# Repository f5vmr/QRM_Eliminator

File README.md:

A mistake in the downloaded zip file!!
The PCB is not designed with Diptrace but with KiCad and the version it was made with can be down loaded free from here - https://www.filehorse.com/download-kicad/55035/download/#google_vignette

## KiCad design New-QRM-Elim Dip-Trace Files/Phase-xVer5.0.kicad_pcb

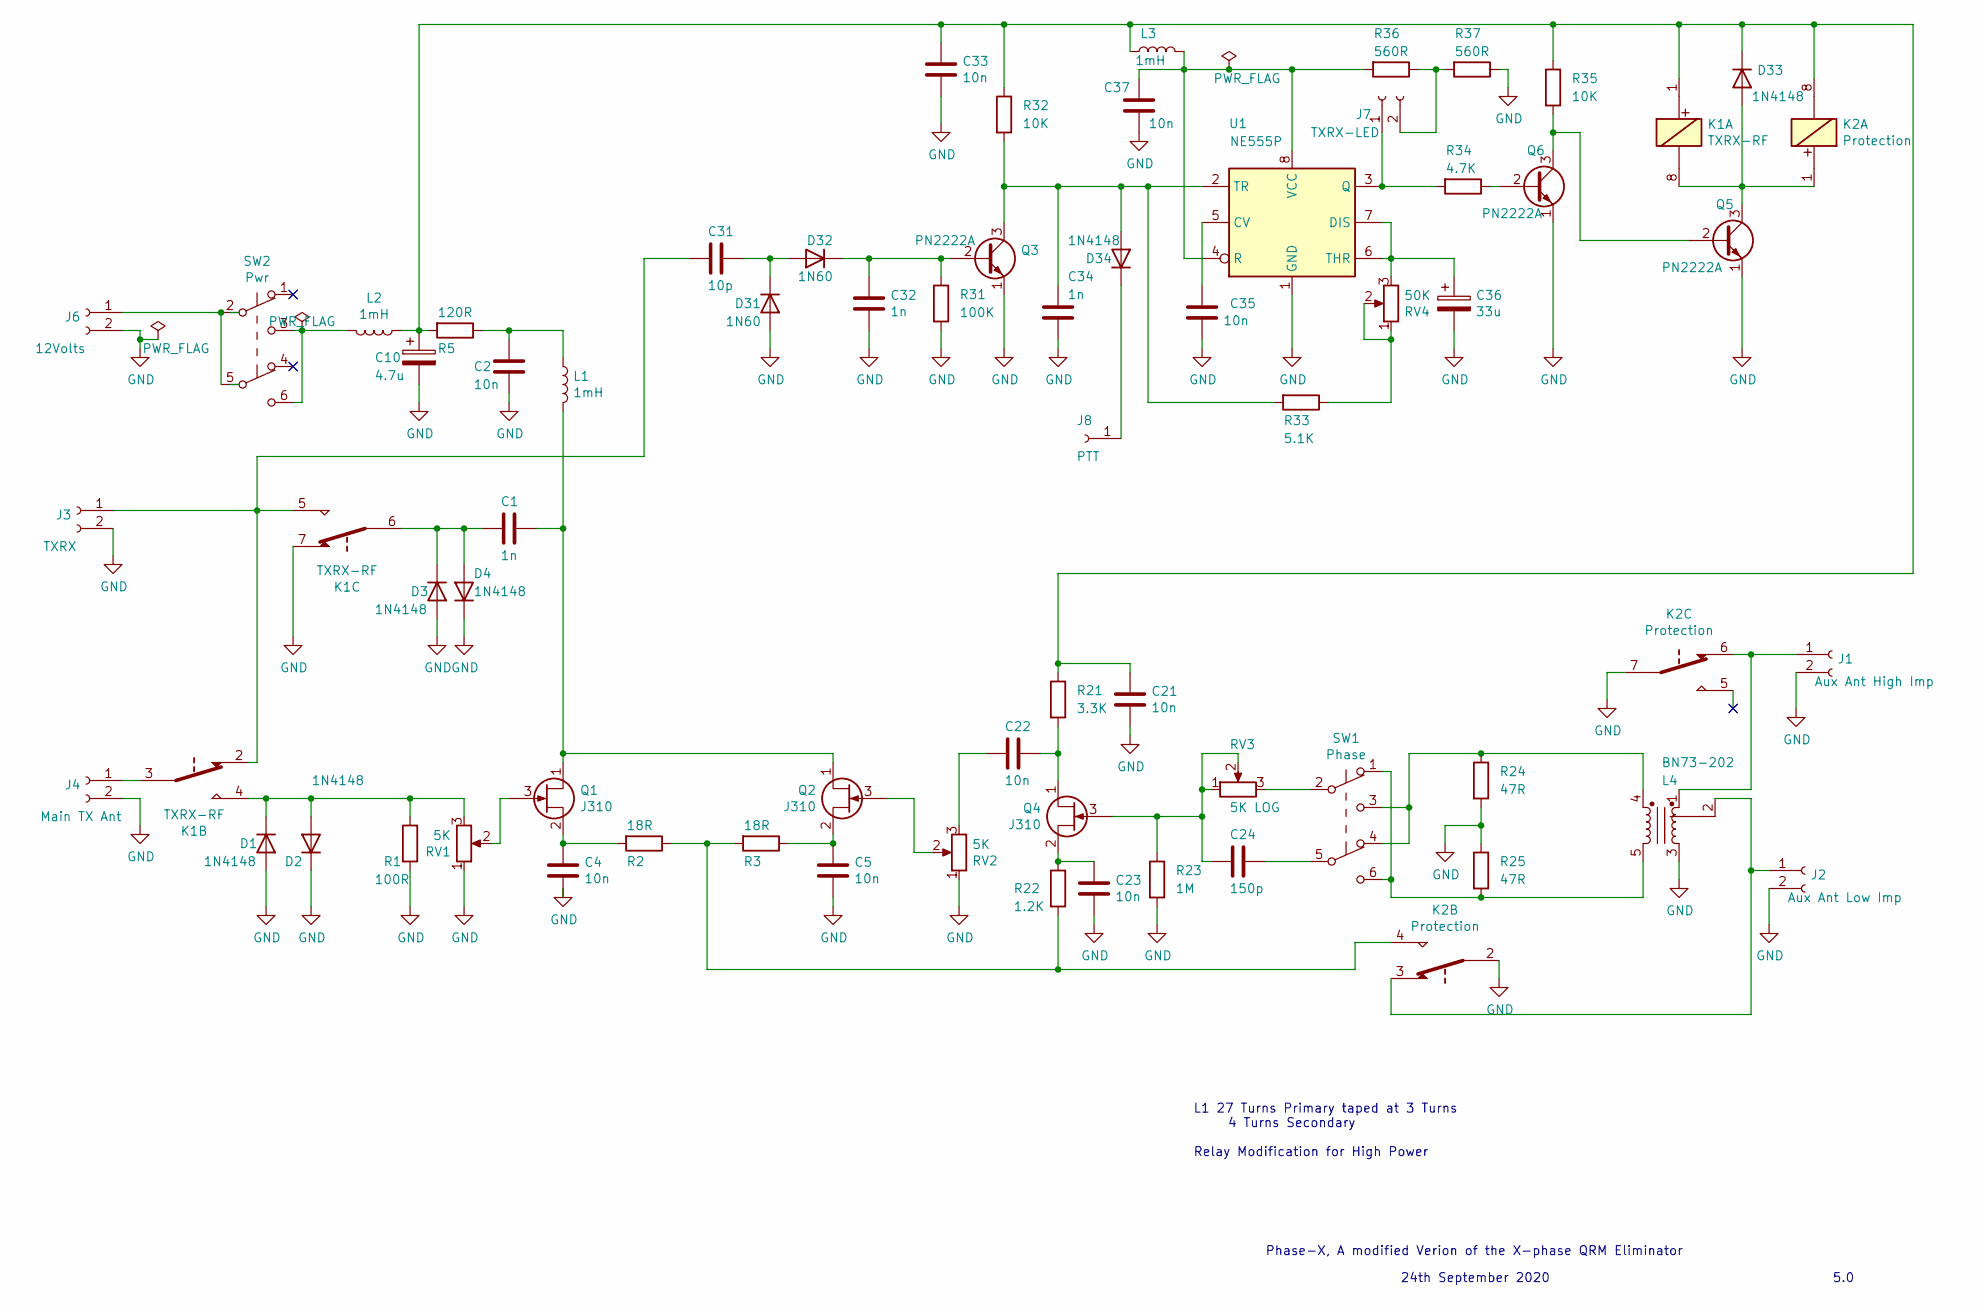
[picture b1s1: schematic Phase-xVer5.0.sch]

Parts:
C1, C32, C34: 1n; CeramicDisc_P5.0mm
C2, C4, C5, C21, C22, C23, C33, C35, C37: 10n; CeramicDisc_P5.0mm
C10: 4.7u; Small_Tant_Elect
C24: 150p; CeramicDisc_P7.5_3pin
C31: 10p; CeramicDisc_P5.0mm
C36: 33u; Small_Tant_Elect
D1, D2, D3, D4, D33, D34: 1N4148; Signal_Diode
D31, D32: 1N60; Signal_Diode
J1: Aux Ant High Imp; Connector
J2: Aux Ant Low Imp; Connector
J3: TXRX; Connector
J4: Main TX Ant; Connector
J6: 12Volts; 2Pin_Molex
J7: TXRX-LED; 2Pin_Molex
J8: PTT; SingleConnector
K1: TXRX-RF; Relay_DPDT_Omron_G2RL
K2: Protection; Relay_DPDT_Omron
L1, L2, L3: 1mH; Inductor
L4: BN73-202
Q1, Q2, Q4: J310; TO-92_Wide
Q3, Q5, Q6: PN2222A; TO-92_Wide
R1: 100R; R_L6.3mm__P10.16mm_Pad2.2mm
R2, R3: 18R; R_L6.3mm__P10.16mm_Pad2.2mm
R5: 120R; R_L6.3mm__P10.16mm_Pad2.2mm
R21: 3.3K; R_L6.3mm__P10.16mm_Pad2.2mm
R22: 1.2K; R_L6.3mm__P10.16mm_Pad2.2mm
R23: 1M; R_L6.3mm__P10.16mm_Pad2.2mm
R24, R25: 47R; R_L6.3mm__P10.16mm_Pad2.2mm
R31: 100K; R_L6.3mm__P10.16mm_Pad2.2mm
R32, R35: 10K; R_L6.3mm__P10.16mm_Pad2.2mm
R33: 5.1K; R_L6.3mm__P10.16mm_Pad2.2mm
R34: 4.7K; R_L6.3mm__P10.16mm_Pad2.2mm
R36, R37: 560R; R_L6.3mm__P10.16mm_Pad2.2mm
RV1, RV2: 5K; Potentiometer_T-16H_Single_Horizontal
RV3: 5K LOG; Potentiometer_T-16H_Single_Horizontal
RV4: 50K; Preset
SW1: Phase; SW_Push_DPDT-P0.1mil
SW2: Pwr; SW_Push_DPDT-P0.1mil
U1: NE555P; DIP8

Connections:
GND: C2.2, C4.2, C5.2, C10.2, C21.2, C23.2, C32.2, C33.2, C34.2, C35.2, C36.2, C37.2, D1.2 (A), D2.1 (K), D3.2 (A), D4.1 (K), D31.2 (A), J1.2, J2.2, J3.2, J4.2, J6.2, K1.7, K2.2, K2.7, L4.3, Q3.1 (E), Q5.1 (E), Q6.1 (E), R1.2, R23.2, R24.2, R25.1, R31.2, R37.1, RV1.1, RV2.1, U1.1 (GND)
unnamed: C1.1, L1.2, Q1.1 (D), Q2.1 (D)
unnamed: C1.2, D3.1 (K), D4.2 (A), K1.6
unnamed: C2.1, L1.1, R5.1
unnamed: C4.1, Q1.2 (S), R2.2
unnamed: C5.1, Q2.2 (S), R3.1
unnamed: C10.1, C21.1, C33.1, D33.1 (K), K1.1, K2.8, L2.1, L3.1, R5.2, R21.1, R32.1, R35.1
unnamed: C22.1, Q4.1 (D), R21.2
unnamed: C22.2, RV2.3
unnamed: C23.1, Q4.2 (S), R22.1
unnamed: C24.1, SW1.5 (B)
unnamed: C24.2, Q4.3 (G), R23.1, RV3.1, RV3.2
unnamed: C31.1, D31.1 (K), D32.2 (A)
unnamed: C31.2, J3.1, K1.2, K1.5
unnamed: C32.1, D32.1 (K), Q3.2 (B), R31.1
unnamed: C34.1, D34.2 (A), Q3.3 (C), R32.2, R33.2, U1.2 (TR)
unnamed: C35.1, U1.5 (CV)
unnamed: C36.1, RV4.3, U1.6 (THR), U1.7 (DIS)
unnamed: C37.1, L3.2, R36.2, U1.4 (R), U1.8 (VCC)
unnamed: D1.1 (K), D2.2 (A), K1.4, R1.1, RV1.3
unnamed: D33.2 (A), K1.8, K2.1, Q5.3 (C)
unnamed: D34.1 (K), J8.1
unnamed: J1.1, K2.6, L4.1
unnamed: J2.1, K2.3, L4.2
unnamed: J4.1, K1.3
unnamed: J6.1, SW2.2 (B), SW2.5 (B)
unnamed: J7.1, R34.2, U1.3 (Q)
unnamed: J7.2, R36.1, R37.2
unnamed: K2.4, R2.1, R3.2, R22.2
unnamed: L2.2, SW2.3 (C), SW2.6 (C)
unnamed: L4.4, R24.1, SW1.3 (C), SW1.4 (A)
unnamed: L4.5, R25.2, SW1.1 (A), SW1.6 (C)
unnamed: Q1.3 (G), RV1.2
unnamed: Q2.3 (G), RV2.2
unnamed: Q5.2 (B), Q6.3 (C), R35.2
unnamed: Q6.2 (B), R34.1
unnamed: R33.1, RV4.1, RV4.2
unnamed: RV3.3, SW1.2 (B)

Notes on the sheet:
L1 27 Turns Primary taped at 3 Turns 4 Turns Secondary Relay Modification for High Power
Phase-X, A modified Verion of the X-phase QRM Eliminator
5.0
24th September 2020

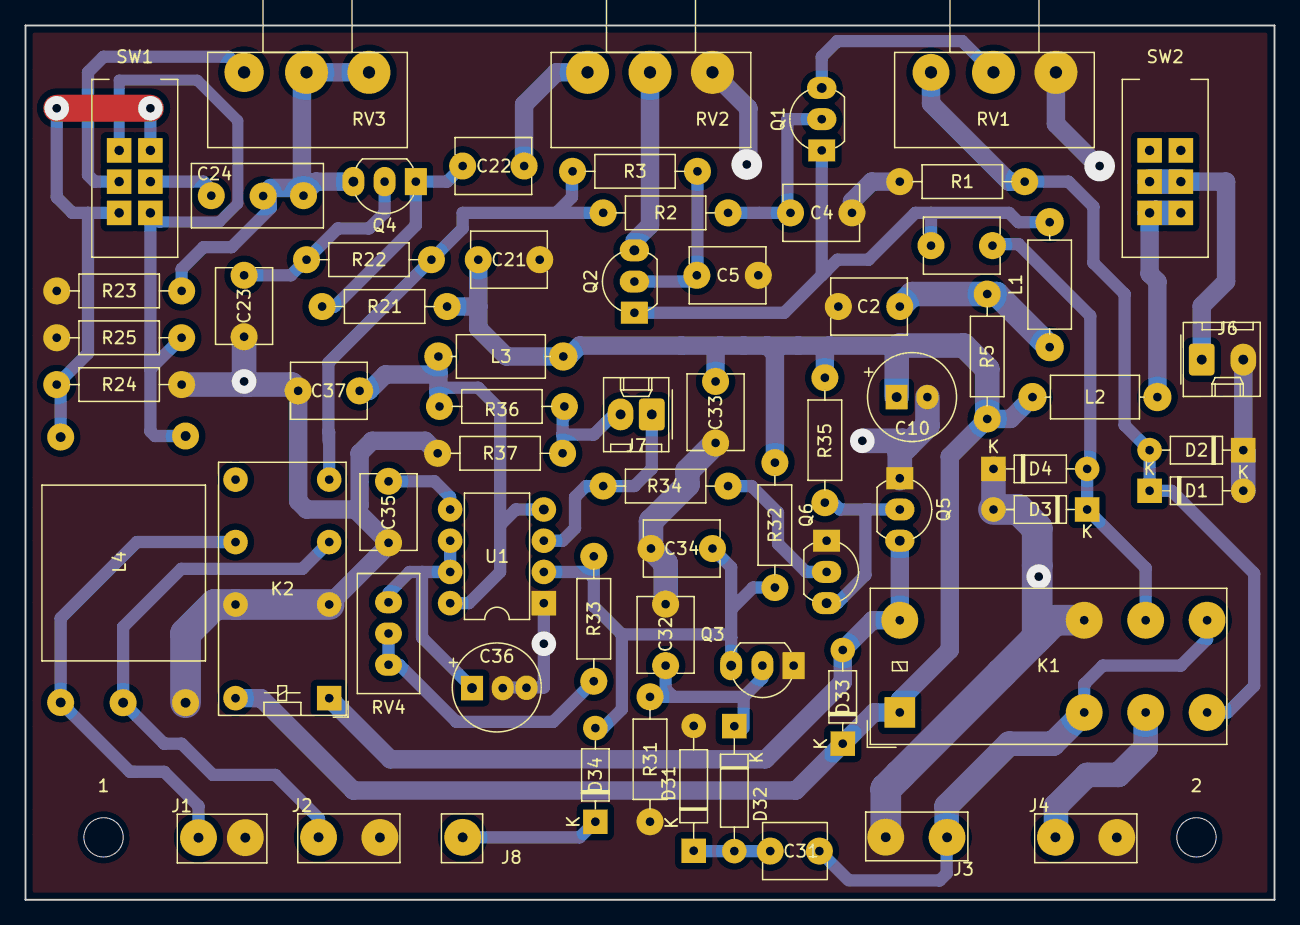
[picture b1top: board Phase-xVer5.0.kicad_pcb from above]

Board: 2 copper layers, 101.6 x 71.1 mm, 67 parts (0 on the bottom side), 38 nets.

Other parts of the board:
1, 2: M3; MountingHole_3.2mm_M3

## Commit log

2025-05-26 Create DipTrace V4.1 Install
